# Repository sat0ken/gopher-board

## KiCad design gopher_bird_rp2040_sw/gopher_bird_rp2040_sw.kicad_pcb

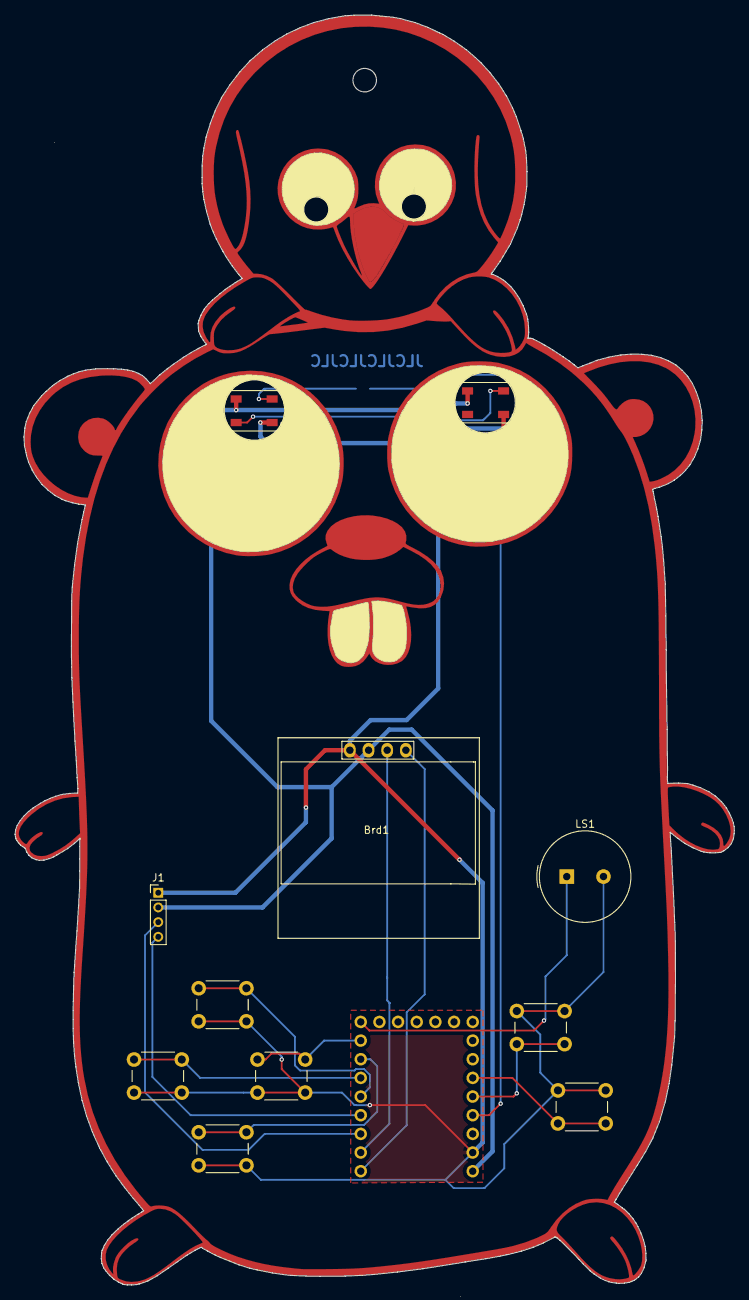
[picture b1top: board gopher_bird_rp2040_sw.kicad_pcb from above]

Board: 2 copper layers, 97.9 x 172.8 mm, 13 parts (1 on the bottom side), 16 nets.

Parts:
Brd1: SSD1306; 128x64OLED
D1, D2: WS2812B; LED_WS2812B_PLCC4_5.0x5.0mm_P3.2mm
J1: Conn_01x04_Pin; PinHeader_1x04_P2.00mm_Vertical
LS1: Speaker; Buzzer_TDK_PS1240P02BT_D12.2mm_H6.5mm
R2: 330; R_0805_2012Metric
SW1, SW2, SW3, SW4, SW5, SW6: SW_Push; SW_PUSH_6mm_H4.3mm
U1: my-rp2040-zero

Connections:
/GP29: R2.1, U1.29 (GP29)
/SCL: Brd1.3 (SCL), U1.1 (GP1)
/SCL1: J1.4, U1.3 (GP3)
/SDA: Brd1.4 (SDA), U1.0 (GP0)
/SDA1: J1.3, U1.2 (GP2)
GND: Brd1.1 (GND), D1.3 (VSS), D2.3 (VSS), J1.1, LS1.2, SW1.2, SW2.2, SW3.2, SW4.2, SW5.1, SW6.1, U1.31 (GND)
unnamed: D1.4 (DIN), R2.2
unnamed: D1.2 (DOUT), D2.4 (DIN)
unnamed: SW1.1, U1.4 (GP4)
unnamed: SW2.1, U1.5 (GP5)
unnamed: SW3.1, U1.6 (GP6)
unnamed: SW4.1, U1.7 (GP7)
unnamed: LS1.1, U1.8 (GP8)
unnamed: SW6.2, U1.27 (GP27)
unnamed: SW5.2, U1.28 (GP28)
VCC: Brd1.2 (VCC), D1.1 (VDD), D2.1 (VDD), J1.2, U1.32 (5v)

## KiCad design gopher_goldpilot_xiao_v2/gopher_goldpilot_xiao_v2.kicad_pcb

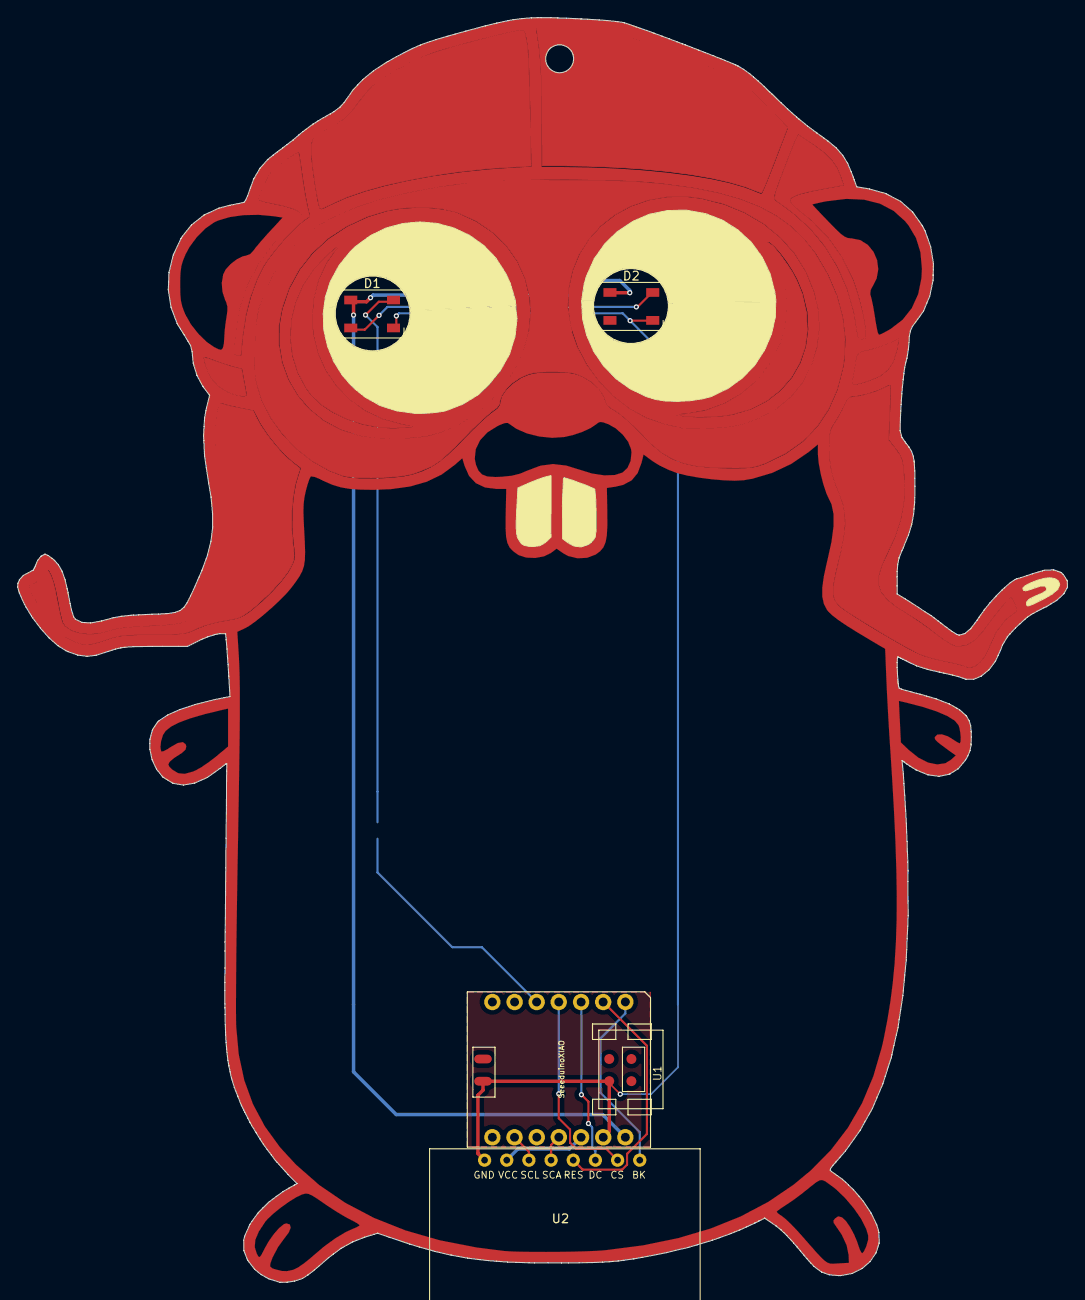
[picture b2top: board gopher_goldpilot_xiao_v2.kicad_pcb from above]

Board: 2 copper layers, 120.3 x 144.9 mm, 5 parts (1 on the bottom side), 12 nets.

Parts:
D1, D2: WS2812B; LED_WS2812B_PLCC4_5.0x5.0mm_P3.2mm
R2: 330; R_0805_2012Metric
U1: SeeeduinoXIAO; Seeeduino XIAO-MOUDLE14P-2.54-21X17.8MM_PinSocket
U2: ST7789_240x240; st7789_135x240

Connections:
/3v3: U1.12, U2.2
/BUK: U1.1, U2.8
/CS: U1.4, U2.7
/DC: U1.3, U2.6
/PA8: R2.1, U1.5
/RES: U1.2, U2.5
/SCK: U1.9, U2.3
/SDA: U1.11, U2.4
GND: D1.3, D2.3, U1.13, U1.16, U1.20, U2.1
unnamed: D1.2, D2.4
unnamed: D1.4, R2.2
VCC: D1.1, D2.1, U1.14, U1.15
